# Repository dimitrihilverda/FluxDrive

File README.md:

# FluxDrive

An Amiga floppy drive emulator built around one ESP32-S3: no Gotek, no second microcontroller. It plugs into the
A500's internal floppy connector, holds a disk image in PSRAM and generates the MFM flux stream itself. Disk
images come from the [GTi](https://github.com/mesarim/Gotek-Touchscreen-interface) touchscreen over ESP-NOW, or
from a phone over WiFi. The design starts from Mez's OMEGAWARE FluxDrive hardware design document (see
[Credits](#credits)).

Status: v1 hardware (rev A) designed and reviewed: schematic, 4-layer layout (DRC clean) and JLCPCB production
files. It can be ordered once the checks under [Before ordering](#before-ordering) pass. Not built yet; the
firmware is a separate project.

| Where | What |
|---|---|
| `docs/superpowers/specs/` | design specs (start with the v1 hardware design) |
| `docs/input/` | the documents this design builds on: Mez's OMEGAWARE FluxDrive HW design v0.1, breadboard measurements |
| `docs/reviews/` | specialist reviews of the spec, schematic and layout, with what was done about each finding |
| `FluxDrive_Schematic.pdf` | the schematic (generated from `hardware/design.py` by `tools/sch_gen.py`) |
| `FluxDrive.kicad_pcb` | the board (built by `tools/pcb_build.sh`; KiCad 10) |
| `jlcpcb/production_files/` | gerbers and drill files (zip), BOM and CPL for JLCPCB (`tools/jlc_production.sh`) |
| `mech/` | 1:1 fit template (PDF) and a STEP model for a printed dummy (`tools/fit_template.sh`) |
| `docs/images/` | renders of the board, top and bottom |

Related: the breadboard prototype and its firmware live in
[dimitrihilverda/amiga-floppy-emulator](https://github.com/dimitrihilverda/amiga-floppy-emulator).

## Building one

The board is 60 × 54.5 mm, 4 layers. JLCPCB places every SMD part on the top side except the ESP32 module; the
module and the connectors are soldered by hand.

### Before ordering

- **Range test:** check the radio with a WROOM-1 dev board inside the closed A500 (spec §11.5). If the range is
  poor, rev A is not the board to order (the WROOM-1U with an external antenna is the fallback).
- **J1:** check the drawing of the box header C601943: its body must not be longer than 52 mm, or it overhangs
  the east edge (the footprint is 50.84 mm, DIN 41651).
- **J2:** check the outline of the TE 171825-4 (C210162) against its footprint (spec O15).
- **Fit:** print `mech/fit_template.pdf` at 100 % (both scale bars must measure 50 mm and 40 mm) and lay it on
  CN11 in the A500: pin 1 over pin 1, the "A500 FRONT" edge towards the front of the computer. Check that the
  drive's power cable from CN12 reaches J2 (about 6 cm) and that the room under the shield takes the tallest part
  (`mech/FluxDrive.step` has the heights; the USB-C, the buttons and the eFuse are missing from it, none taller
  than 3.3 mm). On Dimitri's A500 both are fine. The rectangle that reaches 14.5 mm past the north edge on the
  template is the module's antenna keep-out, not board.

### Order settings (JLCPCB)

Upload `jlcpcb/production_files/GERBER-FluxDrive.zip`:

| Setting | Value |
|---|---|
| Layers | 4 (the default stackup; no impedance control needed: USB is full speed only) |
| Size | 60 × 54.5 mm, single board (no panel) |
| Thickness | 1.6 mm |
| Surface finish | lead-free HASL or ENIG |
| Via covering | tented |
| Mark on PCB | order number at a specified position (the `JLCJLCJLCJLC` text on the bottom) |
| PCB assembly | yes: Economic (Standard if the form does not offer it for 4 layers), top side, 2 or 5 boards |

Then upload `BOM-FluxDrive.csv` and `CPL-FluxDrive.csv`. They hold the 86 SMD parts that JLC places. Left out
(`tools/jlc_export.py` lists them): the ESP32 module U1, which you place yourself (`tools/assembly.py`; its pads get
no solder paste, see below), the unfitted pads, the test pads, the fiducials and every through-hole part.

### Check in JLC's placement preview

Before paying, look at every part below in JLC's preview; fix a wrong rotation there.

- **U2, U3, U4** (74LVC14A, 74LVC07A, SOIC-14): pin 1 at the south-west corner of each. The CPL gives SOIC the same
  correction as the TSSOP that JLC placed on the Nano-Tek; the JLCPCB Tools default would be 270°.
- **U1** (ESP32-S3-WROOM-1) is not placed by JLC: the preview shows its pads empty, and they come without paste.
- **U5** (TPS259531, WSON-8 with exposed pad), **U6** (TLV62569, SOT-23-5), **U7** (USBLC6-2SC6, SOT-23-6):
  pin 1 dot.
- **D1, D2** (SS34): cathode band to the west. **D3** (LED): cathode to the west.
- **J3** (USB-C): the opening flush with the west edge (the shell reaches 0.18 mm past it).
- **SW1, SW2**: the four pads on the pads.

### Soldering by hand

| Ref | Part | LCSC | Notes |
|---|---|---|---|
| U1 | ESP32-S3-WROOM-1-N16R8 module (exactly this variant) | C2913202 | SMD: antenna to the north edge, pin 1 at the north-west. The pads come bare (no paste from JLC, so the module sits flat). Solder the large ground pad underneath (pin 41) too, for ground and heat: flux or paste on the pads, then hot air or a hot plate. An iron alone reaches only the edge pads. Solder it before the connectors, while the board still lies flat |
| J1 | 2×17 box header, 2.54 mm, vertical | C601943 | or, to plug the board straight onto CN11, a 2×17 female socket on the bottom side (see the note on the silkscreen); pin 1 is the square pad |
| J2 | TE 171825-4 floppy power header, vertical | C210162 | polarised; pin 1 = +5 V at the north end |
| J4 | 1×6 pin header, 2.54 mm | — | optional: UART recovery (TX, RX, EN, IO0, 3V3, GND from the ESP32's side) |
| J5 | 1×6 pin header, 2.54 mm | — | optional: spare GPIO13, 14, 47, 48, 3V3, GND |

- **J3's shell legs:** the four through-hole legs of the USB-C receptacle get no solder paste. Check them on
  delivery; if they are bare, solder them from the bottom side (they carry the plugging force, not the SMD pins).
- **After soldering J1:** `/CHNG_D` runs 0.25–0.30 mm past the row of J1's ground pins, on both sides. With the
  board unpowered, beep between U4 pin 10 (`/CHNG_D`) and J1 pin 1 (GND): a steady beep means a solder bridge or
  a scratched mask there, and the Amiga would see a disk change all the time.

The unfitted pads (0603 unless noted), only if bring-up asks for them: C1–C4 220 pF input filters on STEP, SEL0,
SEL1 and MTR0; R16 and R25 1 kΩ pull-ups for the two /MTR0 pins; C16 15 pF buck feed-forward; C21/C22 10 pF on
USB D+/D−; R49 1 Ω + C15 4.7 µF damper on V5SYS (then change C13 from 10 µF to 4.7 µF); D4 SMAJ13A TVS (SMA) on
the power input.

### Power: read this first

- The board takes its power from the A500's drive power connector CN12, through the drive's power cable on J2.
  **Never plug or unplug it with the A500 switched on.** A mini-Berg plug forced on the wrong way round puts
  +12 V on the 5 V pin: the eFuse survives that only when the plug goes on with the power off.
- +12 V (J2 pin 4) is not connected on the board.
- The 34-pin cable without the power cable is not supported: the bus pull-ups then hang on a dead rail.
- USB-C and the A500 may power the board at the same time; neither can feed the other.

### Flashing

Over USB-C: the ESP32-S3's USB-Serial/JTAG enters download mode by itself (`idf.py flash`, `esptool.py`). If the
firmware has taken GPIO19/20 or put the chip to sleep: hold BOOT, press and release RESET, release BOOT, and flash
again. If USB does not work at all, J4 takes a 3.3 V USB-serial adapter (its RX to J4 TX, its TX to J4 RX, GND;
IO0 to GND and a pulse on EN for download mode).

### Test pads

1.0 mm pads on the top side, for a probe. x from the west edge, y from the north (antenna) edge, in mm.

| Pad | Net | x | y | | Pad | Net | x | y |
|---|---|---|---|---|---|---|---|---|
| TP1 | /DKRD (connector) | 50.5 | 53.1 | | TP9 | /MTR0 (connector) | 32.7 | 53.1 |
| TP2 | DKRD_N (ESP32) | 42.6 | 31.8 | | TP10 | MTR0 (ESP32) | 30.8 | 33.7 |
| TP3 | /INDEX (connector) | 22.6 | 53.1 | | TP11 | +5V_A | 14.0 | 32.9 |
| TP4 | INDEX_N (ESP32) | 42.4 | 28.4 | | TP12 | V5SYS | 14.6 | 22.5 |
| TP5 | /SEL0 (connector) | 25.1 | 53.1 | | TP13 | VBUS | 12.2 | 22.6 |
| TP6 | SEL0 (ESP32) | 42.6 | 34.3 | | TP14 | +3V3 | 13.9 | 8.1 |
| TP7 | /STEP (connector) | 37.8 | 53.1 | | TP15 | ESP_EN | 13.9 | 11.8 |
| TP8 | STEP (ESP32) | 42.4 | 26.1 | | TP16 | GND | 55.6 | 53.1 |

The connector-side pads sit in the strip south of J1, each between two ground pins.

### Rebuilding the files

KiCad 10, Python 3 with pytest, Java 17 and Freerouting 1.9 (`~/.kicad-mcp/freerouting.jar`):

```bash
bash tools/export_netlist.sh && python -m pytest -q    # schematic and its tests
bash tools/pcb_build.sh                                # the board: placement, routing, DRC (15-60 min)
bash tools/jlc_production.sh                           # gerbers, BOM and CPL
```

## Credits

- **Mez** ([mesarim](https://github.com/mesarim)): the *OMEGAWARE FluxDrive Hardware Design Document, Rev 0.1*
  ([`docs/input/OMEGAWARE_FluxDrive_HW_Design_v0.1.md`](docs/input/OMEGAWARE_FluxDrive_HW_Design_v0.1.md)), the input
  this design is built on: one ESP32-S3 on the Shugart bus that generates the MFM flux itself and gets its disk
  images from the GTi over ESP-NOW, the bus interface, the bench gate and the bring-up order. The v1 spec says where
  it follows that document and where it departs from it.
- **Dimmy (Dimitri Hilverda)**: the v1 hardware, from the spec to the board and the production files.
- Disk images come from the [GTi](https://github.com/mesarim/Gotek-Touchscreen-interface) touchscreen.

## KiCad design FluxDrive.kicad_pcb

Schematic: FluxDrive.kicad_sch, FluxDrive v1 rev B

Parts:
C1, C2, C3, C4: 220pF; C_0603_1608Metric; not fitted
C5, C6, C7, C8, C9, C10, C16, C19, C21, C26, C30, C31, C32, C33, C36, C37, C38, C39, C40, C41, C42: 100nF; C_0402_1005Metric; LCSC C1525
C11, C13, C27, C34, C35: 1uF; C_0402_1005Metric; LCSC C52923
C12, C14: 22nF; C_0402_1005Metric; LCSC C1532
C15, C24, C25: 22uF; C_0805_2012Metric; LCSC C45783
C17, C18: 47uF; C_1206_3216Metric; LCSC C96123
C20: 10uF; C_0603_1608Metric; LCSC C19702
C22: 4.7uF; C_0603_1608Metric; not fitted
C23: 15pF; C_0603_1608Metric; not fitted
C28, C29: 10pF; C_0603_1608Metric; not fitted
C43, C44, C45: 100nF; C_0603_1608Metric; not fitted
D1, D2: SS34; D_SMA; LCSC C8678
D3: LED red; LED_0603_1608Metric; LCSC C2286
D4: SMAJ13A; D_SMA; not fitted
D5, D6: 1N4148W; D_SOD-123; LCSC C81598
FID1, FID2, FID3: Fiducial; Fiducial_1mm_Mask2mm
H1, H2: 3.2mm; MountingHole_3.2mm_M3
J1: Amiga floppy 34; IDC-Header_2x17_P2.54mm_Vertical; LCSC C601943
J2: Floppy power; 171825-4; LCSC C210162
J3: USB-C; USB-C-SMD_TYPE-C16PIN; LCSC C393939
J4: UART / recovery; PinHeader_1x06_P2.54mm_Vertical
J5: Spare / OLED; PinHeader_1x04_P2.54mm_Vertical
J6: Original drive; IDC-Header_2x17_P2.54mm_Vertical; LCSC C601943
J7: DF0 switch; PinHeader_1x03_P2.54mm_Vertical
J8: Drive power; 171825-4; LCSC C210162
J9: RST wire; TestPoint_THTPad_D1.5mm_Drill0.7mm
J10: MTRX wire; TestPoint_THTPad_D1.5mm_Drill0.7mm
JP1: bypass SEL; SolderJumper-3_P1.3mm_Bridged12_RoundedPad1.0x1.5mm
JP2: bypass MTR; SolderJumper-3_P1.3mm_Bridged12_RoundedPad1.0x1.5mm
JP3: mode 4 SEL; SolderJumper-3_P1.3mm_Bridged12_RoundedPad1.0x1.5mm
JP4: mode 4 MTR; SolderJumper-3_P1.3mm_Bridged12_RoundedPad1.0x1.5mm
JP5: DF0 at power-on; SolderJumper-3_P1.3mm_Bridged12_RoundedPad1.0x1.5mm
JP6: REAL clear; SolderJumper-2_P1.3mm_Open_RoundedPad1.0x1.5mm
JP7: REAL preset; SolderJumper-2_P1.3mm_Open_RoundedPad1.0x1.5mm
L1: 2.2uH; L_Sunlord_SWPA4020S; LCSC C83423
R1, R4, R7, R22, R25, R47, R76, R77: 4K7; R_0402_1005Metric; LCSC C25900
R2, R5, R8, R11, R15, R19, R23, R26, R28: 100; R_0402_1005Metric; LCSC C25076
R3, R6, R9, R12, R16, R20, R24, R27, R29, R32, R33, R51, R68, R69, R85: 100K; R_0402_1005Metric; LCSC C25741
R10, R13, R14, R17, R21, R53, R63, R70, R71, R74, R75, R83: 1K; R_0402_1005Metric; LCSC C11702
R18: 1K; R_0603_1608Metric; not fitted
R30: 4K7; R_0603_1608Metric; not fitted
R31: 100; R_0603_1608Metric; not fitted
R34, R36, R38, R40, R42, R44, R46, R55, R56, R59, R64, R65, R66, R67, R72, R73, R78, R79, R80, R82: 10K; R_0402_1005Metric; LCSC C25744
R35, R37, R39, R41, R43, R45, R81: 33; R_0402_1005Metric; LCSC C25105
R48: 2K2; R_0402_1005Metric; LCSC C25879
R49: 1K37; R_0402_1005Metric; LCSC C423239
R50: 1R; R_0603_1608Metric; not fitted
R52: 22K; R_0402_1005Metric; LCSC C25768
R54: 1K5; R_0402_1005Metric; LCSC C25867
R57, R58: 5K1; R_0402_1005Metric; LCSC C25905
R60, R61: 22; R_0402_1005Metric; LCSC C25092
R62: 470; R_0402_1005Metric; LCSC C25117
R84: 33; R_0603_1608Metric; not fitted
SW1: BOOT; SW_Push_1P1T_XKB_TS-1187A; LCSC C318884
SW2: RESET; SW_Push_1P1T_XKB_TS-1187A; LCSC C318884
TP1: _DKRD; TestPoint_Pad_D1.0mm
TP2: DKRD_N; TestPoint_Pad_D1.0mm
TP3: _INDEX; TestPoint_Pad_D1.0mm
TP4: INDEX_N; TestPoint_Pad_D1.0mm
TP5: _SEL0; TestPoint_Pad_D1.0mm
TP6: SEL0; TestPoint_Pad_D1.0mm
TP7: _STEP; TestPoint_Pad_D1.0mm
TP8: STEP; TestPoint_Pad_D1.0mm
TP9: _MTR0; TestPoint_Pad_D1.0mm
TP10: MTR0; TestPoint_Pad_D1.0mm
TP11: +5V_A; TestPoint_Pad_D1.0mm
TP12: V5SYS; TestPoint_Pad_D1.0mm
TP13: VBUS; TestPoint_Pad_D1.0mm
TP14: +3V3; TestPoint_Pad_D1.0mm
TP15: ESP_EN; TestPoint_Pad_D1.0mm
TP16: GND; TestPoint_Pad_D1.0mm
TP17: SEL_FD; TestPoint_Pad_D1.0mm
TP18: REAL_SEL; TestPoint_Pad_D1.0mm
TP19: REAL_MTR; TestPoint_Pad_D1.0mm
TP20: DF0_FD; TestPoint_Pad_D1.0mm
TP21: DF1_EN; TestPoint_Pad_D1.0mm
TP22: MODE_CLK; TestPoint_Pad_D1.0mm
U1: ESP32-S3-WROOM-1-N16R8; ESP32-S3-WROOM-1; LCSC C2913202
U2, U3: 74LVC14A; SOIC-14_3.9x8.7mm_P1.27mm; LCSC C133541
U4: 74LVC07A; SOIC-14_3.9x8.7mm_P1.27mm; LCSC C176925
U5, U9: TPS259531; Texas_DSG0008A_WSON-8-1EP_2x2mm_P0.5mm_EP0.9x1.6mm; LCSC C2155674
U6: TLV62569DBVR; SOT-23-5; LCSC C141836
U7: USBLC6-2SC6; SOT-23-6; LCSC C2687116
U8: 74LVC74A; TSSOP-14_4.4x5mm_P0.65mm; LCSC C6100
U10, U11: 74LVC32A; TSSOP-14_4.4x5mm_P0.65mm; LCSC C6087
U12, U13, U14, U15, U16: 74LVC1G157; SOT-363_SC-70-6; LCSC C135822
U17: SN74LVC2G07; SOT-23-6; LCSC C37708
U18: SN74LVC2G06; SOT-23-6; LCSC C402162
U19: SN74LVC1G06; SOT-23-5; LCSC C840103
U20: SN74LVC1G38; SOT-23-5; LCSC C2867613
U21: 74LVC1G157; SOT-363_SC-70-6; LCSC C135822; not fitted
U22: SN74LVC1G175; SOT-23-6; LCSC C128412; not fitted
U23: SN74LVC1G38; SOT-23-5; LCSC C2867613; not fitted

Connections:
/+3V3: C5.1, C6.1, C7.1, C8.1, C9.1, C10.1, C23.1, C24.1, C25.1, C26.1, C30.1, C31.1, C32.1, C33.1, C38.1, C39.1, C40.1, C41.1, C42.1, C43.1, C44.1, C45.1, D5.1 (K), D6.1 (K), J4.5, J5.2, JP7.2 (B), L1.2, R3.2, R6.2, R9.2, R12.2, R16.2, R20.2, R24.2, R27.2, R29.2, R32.2, R34.2, R36.2, R38.2, R40.2, R42.2, R44.2, R51.1, R55.1, R56.1, R64.2, R65.2, R66.2, R67.2, TP14.1, U1.2 (3V3), U2.14 (VCC), U3.14 (VCC), U4.9, U4.11, U4.14 (VCC), U7.5 (VBUS), U8.14 (VCC), U10.14 (VCC), U11.14 (VCC), U12.5 (VCC), U13.5 (VCC), U14.5 (VCC), U15.5 (VCC), U16.5 (VCC), U17.5 (VCC), U18.5 (VCC), U19.5 (VCC), U20.5 (VCC), U21.5 (VCC), U22.5 (VCC), U23.5 (VCC)
/+5V_A: C17.1, C18.1, C19.1, D1.2 (A), R1.2, R4.2, R7.2, R10.2, R14.2, R18.2, R22.2, R25.2, R30.2, R53.1, R76.2, R77.2, R78.2, R79.2, R80.2, TP11.1, U5.5 (OUT)
/+5V_DRIVE: C15.1, C16.1, J8.1 (5V), U9.5 (OUT)
/+5V_IN: C11.1, C13.1, D4.1 (A1), J2.1 (5V), R46.1, U5.3 (IN), U5.4 (IN), U9.3 (IN), U9.4 (IN)
/+12V: J2.4 (12V), J8.4 (12V)
/AMIGA_PWR: R53.2, R54.1, U1.39 (IO1)
/BOOT: J4.4, R56.2, SW1.1, U1.27 (IO0)
/BUCK_FB: C23.2, R51.2, R52.1, U6.5 (FB)
/BUCK_SW: L1.1, U6.3 (SW)
/BUSY: U11.8, U16.6 (S)
/CHNG_D: R43.1, U17.6
/CHNG_G: U11.3, U17.1
/CHNG_N: R42.1, U1.35 (IO42), U11.1
/CHNG_REQ: R73.1, U1.22 (IO14), U20.1
/CLR_A: JP5.1 (A), JP6.1 (A), R64.1, R75.2, U8.1 (~R)
/CLR_B: C34.1, D5.2 (A), R66.1, U8.13 (~R)
/DF0_FD: R68.1, R70.1, TP20.1, U8.5 (Q), U13.6 (S), U14.6 (S), U15.6 (S), U21.6 (S)
/DF0_REQ: R68.2, U1.25 (IO48), U8.2 (D)
/DF0_STATE: R70.2, U1.20 (IO12)
/DF1_EN: R69.1, R71.1, TP21.1, U8.9 (Q), U12.6 (S), U22.6 (~CLR)
/DF1_REQ: R69.2, U1.21 (IO13), U8.12 (D)
/DF1_STATE: R71.2, U1.12 (IO8)
/DIR: U1.7 (IO7), U2.2
/DIR_B: R5.2, R6.1, U2.1
/DKRD_D: R35.1, U4.4
/DKRD_G: U4.3, U10.3
/DKRD_N: R34.1, TP2.1, U1.31 (IO38), U10.1
/DKWD: U1.5 (IO5), U2.4
/DKWD_B: R23.2, R24.1, U2.3
/DKWE: U1.9 (IO16), U2.10
/DKWE_B: R26.2, R27.1, U2.11
/DRV_DVDT: C14.1, U9.1 (dVdt)
/DRV_ILM: R49.1, U9.7 (ILM)
/EFUSE_DVDT: C12.1, U5.1 (dVdt)
/EFUSE_EN: R46.2, R47.1, U5.2 (EN/UVLO), U9.2 (EN/UVLO)
/EFUSE_ILM: R48.1, U5.7 (ILM)
/ESP_EN: C27.1, J4.3, R55.2, SW2.1, TP15.1, U1.3 (EN)
/ESP_RXD0: J4.2, U1.36 (RXD0)
/ESP_TXD0: R62.1, U1.37 (TXD0)
/GND: C1.2, C2.2, C3.2, C4.2, C5.2, C6.2, C7.2, C8.2, C9.2, C10.2, C11.2, C12.2, C13.2, C14.2, C15.2, C16.2, C17.2, C18.2, C19.2, C20.2, C21.2, C22.2, C24.2, C25.2, C26.2, C27.2, C28.2, C29.2, C30.2, C31.2, C32.2, C33.2, C34.2, C35.2, C36.2, C37.2, C38.2, C39.2, C40.2, C41.2, C42.2, C43.2, C44.2, C45.2, D3.1 (K), D4.2 (A2), J1.1, J1.5, J1.7, J1.9, J1.11, J1.13, J1.15, J1.17, J1.19, J1.21, J1.23, J1.25, J1.27, J1.29, J1.31, J1.33, J2.2 (GND), J2.3 (GND), J3.1 (SHELL), J3.2 (SHELL), J3.3 (SHELL), J3.4 (SHELL), J3.A1B12 (GND), J3.B1A12 (GND), J4.6, J5.1, J6.1, J6.5, J6.7, J6.9, J6.11, J6.13, J6.15, J6.17, J6.19, J6.21, J6.23, J6.25, J6.27, J6.29, J6.31, J6.33, J7.2, J8.2 (GND), J8.3 (GND), JP3.1 (A), JP4.1 (A), JP6.2 (B), R33.2, R47.2, R48.2, R49.2, R52.2, R54.2, R57.2, R58.2, R59.2, R72.2, R73.2, R82.2, R85.2, SW1.2, SW2.2, TP16.1, U1.1 (GND), U1.40 (GND), U1.41 (GND), U2.7 (GND), U3.7 (GND), U4.7 (GND), U5.8 (GND), U5.9 (PAD), U6.2 (GND), U7.2 (GND), U8.7 (GND), U9.8 (GND), U9.9 (PAD), U10.7 (GND), U11.7 (GND), U11.12, U11.13, U12.2 (GND), U12.3 (I0), U13.2 (GND), U14.2 (GND), U15.2 (GND), U16.1 (I1), U16.2 (GND), U17.2 (GND), U18.2 (GND), U19.3 (GND), U20.3 (GND), U21.2 (GND), U21.3 (I0), U22.2 (GND), U23.3 (GND)
/GPIO3: J5.4, U1.15 (IO3)
/GPIO18: J5.3, U1.11 (IO18)
/ID_D: R84.1, U23.4
/INDEX_D: R45.1, U17.4
/INDEX_G: U11.6, U17.3
/INDEX_N: R44.1, TP4.1, U1.32 (IO39), U11.4
/J6_MTR: J6.4, J6.16, JP2.2 (C)
/J6_MTR_D: JP2.1 (A), R77.1, U18.4
/J6_PIN6: J6.6, R78.1
/J6_PIN12: J6.12, R79.1
/J6_PIN14: J6.14, R80.1
/J6_SEL: J6.10, JP1.2 (C)
/J6_SEL_D: JP1.1 (A), R76.1, U18.6
/J7_FD: C36.1, J7.1, R74.1
/J7_REAL: C37.1, J7.3, R75.1
/KBRESET: J9.1, R28.1, U19.4
/LED: R63.1, U1.38 (IO2)
/LED_A: D3.2 (A), R63.2
/M4_MOTOR: U3.6, U22.3 (D)
/M4_MTR: JP4.2 (C), U15.1 (I1)
/M4_MTR_N: U3.12, U23.2
/M4_MTR_Q: JP4.3 (B), R33.1, U3.13, U22.4 (Q)
/M4_SEL: JP3.2 (C), U14.1 (I1)
/M4_SEL_Q: JP3.3 (B), R85.1, U21.4 (Y), U23.1
/MODE_CLK: TP22.1, U8.3 (C), U8.11 (C), U16.4 (Y)
/MODE_CLK_REQ: R72.1, U1.24 (IO47), U16.3 (I0)
/MTR0: R21.1, TP10.1, U3.8, U15.3 (I0)
/MTR0_B: C4.1, R19.2, R20.1, U3.9
/MTR0_IO: R21.2, U1.19 (IO11)
/MTRX: J10.1, R30.1, R31.1
/MTRX_B: R31.2, R32.1, U3.5
/POR_A: C35.1, D6.2 (A), JP5.2 (C)
/PRE_A: JP5.3 (B), JP7.1 (A), R65.1, R74.2, U8.4 (~S)
/PRE_B: R67.1, U8.10 (~S)
/RDY_D: R41.1, U4.6
/RDY_G: U4.5, U10.11
/RDY_N: R40.1, U1.23 (IO21), U10.12
/REAL_MTR: TP19.1, U15.4 (Y), U18.3
/REAL_SEL: TP18.1, U14.4 (Y), U18.1
/RST_ACT: R83.1, U3.2
/RST_ACT_IO: R83.2, U1.4 (IO4)
/RST_B: R28.2, R29.1, U3.1
/RST_REQ: R82.1, U1.18 (IO10), U19.2
/SEL0: R13.1, TP6.1, U3.4, U11.9, U13.1 (I1), U14.3 (I0), U20.2
/SEL0_B: C2.1, R11.2, R12.1, U3.3
/SEL0_IO: R13.2, U1.10 (IO17)
/SEL1: R17.1, U3.10, U11.10, U12.1 (I1), U22.1 (C)
/SEL1_B: C3.1, R15.2, R16.1, U3.11
/SEL1_EN: U12.4 (Y), U13.3 (I0), U21.1 (I1)
/SEL1_IO: R17.2, U1.17 (IO9)
/SEL_FD: TP17.1, U2.9, U13.4 (Y)
/SEL_FD_N: U2.8, U10.2, U10.5, U10.10, U10.13, U11.2, U11.5
/SIDE: U1.8 (IO15), U2.6
/SIDE_B: R8.2, R9.1, U2.5
/STEP: TP8.1, U1.6 (IO6), U2.12
/STEP_B: C1.1, R2.2, R3.1, U2.13
/TRK0_D: R37.1, U4.12
/TRK0_G: U4.13, U10.6
/TRK0_N: R36.1, U1.33 (IO40), U10.4
/UART_TX: J4.1, R62.2
/USB_CC1: J3.A5 (CC1), R57.1
/USB_CC2: J3.B5 (CC2), R58.1
/USB_DN: C29.1, R61.2, U1.13 (USB_D-)
/USB_DN_C: J3.A7 (DN1), J3.B7 (DN2), R61.1, U7.1 (I/O1), U7.6 (I/O1)
/USB_DP: C28.1, R60.2, U1.14 (USB_D+)
/USB_DP_C: J3.A6 (DP1), J3.B6 (DP2), R60.1, U7.3 (I/O2), U7.4 (I/O2)
/V5SYS: C20.1, C21.1, D1.1 (K), D2.1 (K), R50.1, TP12.1, U6.1 (EN), U6.4 (VIN)
/V5SYS_DAMP: C22.1, R50.2
/VBUS: D2.2 (A), J3.A4B9 (VBUS), J3.B4A9 (VBUS), R59.1, TP13.1
/VCHNG_D: R81.1, U20.4
/WPROT_D: R39.1, U4.2
/WPROT_G: U4.1, U10.8
/WPROT_N: R38.1, U1.34 (IO41), U10.9
/_CHNG: J1.2, J6.2, R43.2, R81.2
/_DIR: J1.18, J6.18, R4.1, R5.1
/_DKRD: J1.30, J6.30, R35.2, TP1.1
/_DKWD: J1.22, J6.22, R22.1, R23.1
/_DKWE: J1.24, J6.24, R25.1, R26.1
/_INDEX: J1.8, J6.8, R45.2, TP3.1
/_MTR0: J1.16, JP2.3 (B), R18.1, R19.1, TP9.1
/_RDY: J1.34, J6.34, R41.2, R84.2
/_SEL0: J1.10, JP1.3 (B), R10.1, R11.1, TP5.1
/_SEL1: J1.12, R14.1, R15.1
/_SIDE: J1.32, J6.32, R7.1, R8.1
/_STEP: J1.20, J6.20, R1.1, R2.1, TP7.1
/_TRK0: J1.26, J6.26, R37.2
/_WPROT: J1.28, J6.28, R39.2

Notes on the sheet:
A. Floppy connector and bus inputs
B. Bus outputs
C. Power
D. ESP32-S3 module
E. USB-C
F. Headers, buttons, LED, test pads, mechanics
G. Drive pass-through and DF0/DF1 swap

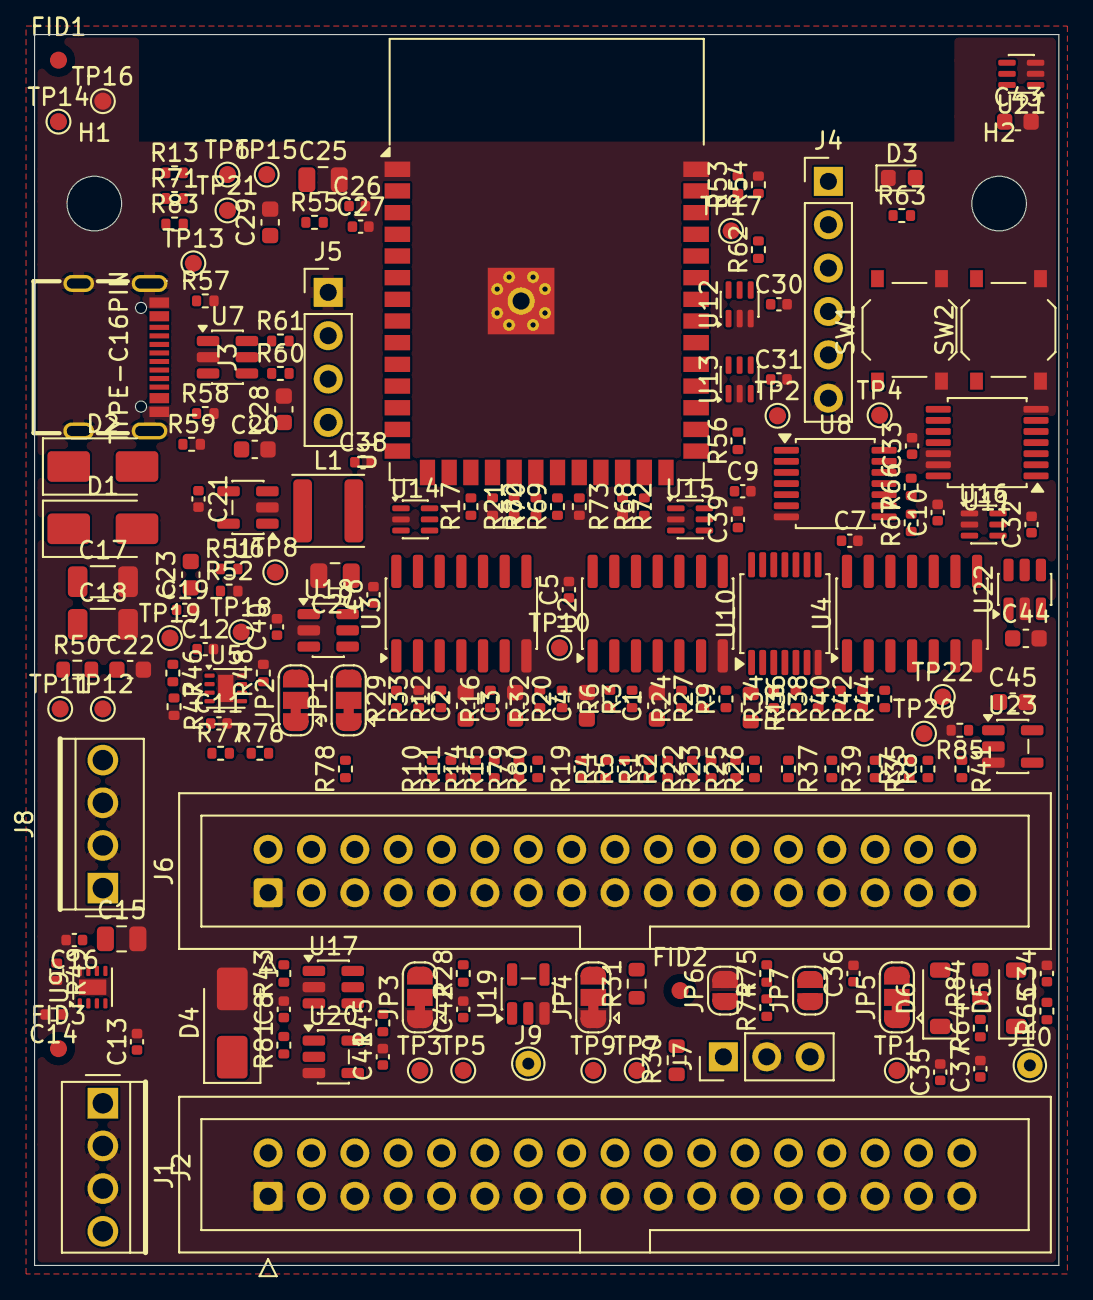
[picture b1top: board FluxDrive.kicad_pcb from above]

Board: 4 copper layers, 60.0 x 72.1 mm, 206 parts (0 on the bottom side), 127 nets, no tracks yet.

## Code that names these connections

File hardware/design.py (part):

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# --- A: connector and inputs -----------------------------------------------------------------------------
EVEN = {2: "_CHNG", 4: None, 6: None, 8: "_INDEX", 10: "_SEL0", 12: "_SEL1", 14: None,
        16: "_MTR0", 18: "_DIR", 20: "_STEP", 22: "_DKWD", 24: "_DKWE", 26: "_TRK0", 28: "_WPROT",
        30: "_DKRD", 32: "_SIDE", 34: "_RDY"}          # rev B spec §7: pins 4, 6, 14 are not used on the A500
j1 = {str(p): ("GND" if p != 3 else None) for p in range(1, 34, 2)}
j1.update({str(p): n for p, n in EVEN.items()})
part("J1", "Connector_Generic:Conn_02x17_Odd_Even", "Amiga floppy 34", "Connector_IDC:IDC-Header_2x17_P2.54mm_Vertical",
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GPIO_NET = {}
buf = {"U2": {"14": "+3V3", "7": "GND", "9": "SEL_FD", "8": "SEL_FD_N"},   # U2's spare makes SEL_FD_N (§4.2)
       "U3": {"14": "+3V3", "7": "GND",
              "1": "RST_B", "2": "RST_ACT",              # rev A's J1 pin 4 gate: the reset wire (§4.8)
              "5": "MTRX_B", "6": "M4_MOTOR",            # rev A's pin 14 gate: mode 4's motor line (§4.7)
              "13": "M4_MTR_Q", "12": "M4_MTR_N"}}       # rev A's pin 6 gate: NOT M4_MTR for the DF1 ID (§4.7)
for sig, conn, pull, gpio, u, pin_in, pin_out, cpad, iso in INPUTS:
    if pull:
        R(pull[0], conn, pull[1], A)
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for sig, conn, gpio, bufr, pin_in, pin_out, orc, (a, b, y) in OUTPUTS:
    R("10K", f"{sig}_N", "+3V3", B)                 # release pull-up, on the OR input (rev B §4.3)
    R("33", f"{sig}_D", conn, B)
    pins_of[orc].update({str(a): f"{sig}_N", str(b): "SEL_FD_N", str(y): f"{sig}_G"})
    pins_of[bufr].update({str(pin_in): f"{sig}_G", str(pin_out): f"{sig}_D"})
    GPIO_NET[gpio] = f"{sig}_N"
part("U4", "74xx:74LCX07", "74LVC07A", SOIC14, pins_of["U4"], B,      # Diodes 74LVC07AS14-13, SO-14
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C("22uF", "+3V3", "GND", P)
R("1K", "+5V_A", "AMIGA_PWR", P)            # 3.0 V at 5 V, 3.5 V at the clamp; stiff enough that the bus
R("1K5", "AMIGA_PWR", "GND", P)             # pull-ups cannot lift it on USB alone (review SESP-1)
PWR_FLAGS = ["GND", "+3V3", "+5V_IN", "V5SYS", "VBUS"]          # +5V_A is driven by the eFuse OUT pin

# --- D: ESP32-S3 module --------------------------------------------------------------------------------------
esp = {"1": "GND", "40": "GND", "41": "GND", "3V3": "+3V3", "EN": "ESP_EN", "IO0": "BOOT", "IO1": "AMIGA_PWR",
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for gpio, net in GPIO_NET.items():
    esp[f"IO{gpio}"] = net
esp.update({"IO47": "MODE_CLK_REQ", "IO48": "DF0_REQ", "IO13": "DF1_REQ", "IO14": "CHNG_REQ",
            "IO10": "RST_REQ", "IO12": "DF0_STATE", "IO8": "DF1_STATE", "IO4": "RST_ACT_IO", "IO18": "GPIO18",
            "IO3": "GPIO3"})
part("U1", "RF_Module:ESP32-S3-WROOM-1", "ESP32-S3-WROOM-1-N16R8", "FluxDrive:ESP32-S3-WROOM-1", esp, E,
     lcsc="C2913202")
C("22uF", "+3V3", "GND", E)
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     {"1": "UART_TX", "2": "ESP_RXD0", "3": "ESP_EN", "4": "BOOT", "5": "+3V3", "6": "GND"}, F, in_bom=False)
HDR4 = "Connector_PinHeader_2.54mm:PinHeader_1x04_P2.54mm_Vertical"
part("J5", "Connector_Generic:Conn_01x04", "Spare / OLED", HDR4,              # rev B §7: GND 3V3 SCL SDA order
     {"1": "GND", "2": "+3V3", "3": "GPIO18", "4": "GPIO3"}, F, in_bom=False)
R("1K", "LED", "LED_A", F)
part("D3", "Device:LED", "LED red", "LED_SMD:LED_0603_1608Metric", {"1": "GND", "2": "LED_A"}, F, lcsc="C2286")
for net in ("_DKRD", "DKRD_N", "_INDEX", "INDEX_N", "_SEL0", "SEL0", "_STEP", "STEP", "_MTR0", "MTR0",
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part("JP4", JP3B[0], "mode 4 MTR", JP3B[2], {"1": "GND", "2": "M4_MTR", "3": "M4_MTR_Q"}, G, in_bom=False)
j6 = {str(p): ("GND" if p != 3 else None) for p in range(1, 34, 2)}
j6.update({str(p): EVEN[p] for p in (2, 8, 18, 20, 22, 24, 26, 28, 30, 32, 34)})
j6.update({"4": "J6_MTR", "16": "J6_MTR", "10": "J6_SEL", "6": "J6_PIN6", "12": "J6_PIN12", "14": "J6_PIN14"})
part("J6", "Connector_Generic:Conn_02x17_Odd_Even", "Original drive", "Connector_IDC:IDC-Header_2x17_P2.54mm_Vertical",
     j6, G, lcsc="C601943")
for net in ("J6_PIN6", "J6_PIN12", "J6_PIN14"):
    R("10K", net, "+5V_A", G)
part("U20", "74xGxx:74LVC1G38", "SN74LVC1G38", "Package_TO_SOT_SMD:SOT-23-5",
     {"1": "CHNG_REQ", "2": "SEL0", "4": "VCHNG_D", "3": "GND", "5": "+3V3"}, G, lcsc="C2867613")
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R("1K", "RST_ACT", "RST_ACT_IO", G)
TP_THT = "TestPoint:TestPoint_THTPad_D1.5mm_Drill0.7mm"
part("J9", "Connector:TestPoint", "RST wire", TP_THT, {"1": "KBRESET"}, G, in_bom=False)   # to _KBRESET (§4.8)
part("J10", "Connector:TestPoint", "MTRX wire", TP_THT, {"1": "MTRX"}, G, in_bom=False)   # to CIA-B pin 17 (§4.7)
mux("U21", "DF0_FD", "GND", "SEL1_EN", "M4_SEL_Q", dnp=True)   # M4_SEL = DF0_FD AND SEL1_EN
part("U22", "74xGxx:74LVC1G175", "SN74LVC1G175", "Package_TO_SOT_SMD:SOT-23-6",   # SN74LVC1G175DBVR
     {"1": "SEL1", "3": "M4_MOTOR", "6": "DF1_EN", "4": "M4_MTR_Q", "2": "GND", "5": "+3V3"}, G, lcsc="C128412",
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
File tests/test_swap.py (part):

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def test_control_gpios(nl):
    """Rev B spec §7: the GPIO map; outputs active-high with 10k pull-downs, read-backs through 1k."""
    want = {47: "MODE_CLK_REQ", 48: "DF0_REQ", 13: "DF1_REQ", 14: "CHNG_REQ", 12: "DF0_STATE", 8: "DF1_STATE",
            18: "GPIO18", 3: "GPIO3"}
    for gpio, net in want.items():
        assert esp_net(nl, gpio) == net, gpio
    for net in ("MODE_CLK_REQ", "CHNG_REQ"):
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    for p in J6_1TO1:
        assert nl.net_of("J6", p) == nl.net_of("J1", p), p
    assert nl.net_of("J6", 10) == "J6_SEL" and nl.net_of("J6", 4) == nl.net_of("J6", 16) == "J6_MTR"
    for p, net in ((6, "J6_PIN6"), (12, "J6_PIN12"), (14, "J6_PIN14")):
        assert nl.net_of("J6", p) == net and pulls(nl, net) == [("10K", "+5V_A")], p
    for p in range(1, 35, 2):
        assert (nl.net_of("J6", p) or "").startswith("unconnected-") if p == 3 else nl.net_of("J6", p) == "GND"
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    from tests.logic import evaluate
    v = evaluate(nl, {"_CHNG": (1, 1), "_INDEX": (1, 1), "_TRK0": (1, 1), "_WPROT": (1, 1), "_DKRD": (1, 1),
                      "_RDY": (1, 1), "KBRESET": (1, 1)})
    for net in ("J6_SEL", "J6_MTR", "J6_PIN6", "J6_PIN12", "J6_PIN14"):
        assert v[net] == 1, net


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    assert [nl.net_of("U22", p) for p in (1, 3, 6, 4)] == ["SEL1", "M4_MOTOR", "DF1_EN", "M4_MTR_Q"]
    assert {nl.net_of("U23", 1), nl.net_of("U23", 2)} == {"M4_SEL_Q", "M4_MTR_N"} and nl.net_of("U23", 4) == "ID_D"
    from tests.fd import dnp_between
    assert len(dnp_between(nl, "ID_D", "_RDY", "R")) == 1
    assert nl.net_of("J10", 1) == "MTRX"


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def test_reset_wire(nl):
    assert nl.net_of("J9", 1) == "KBRESET"
    assert not pulls(nl, "KBRESET")                              # no pull-up on the pad: RP501 on the motherboard
    assert [value(nl, r) for r in parts_between(nl, "KBRESET", "RST_B")] == ["100"]      # into U3 pin 1 (§4.8)
    assert value(nl, "U19") == "SN74LVC1G06"
    assert (nl.net_of("U19", 2), nl.net_of("U19", 4)) == ("RST_REQ", "KBRESET")
    assert pulls(nl, "RST_REQ") == [("10K", "GND")]
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    for bridged, stored in (({"J7": [("1", "2")]}, 0), ({}, 1)):          # J7 on FD; or the GTi chose FD
        bridged = {**bridged, "JP1": [("2", "3")], "JP2": [("2", "3")]}
        v = evaluate(nl, amiga(1, 0, 0), state={("U8", "A"): stored, ("U8", "B"): 0}, bridged=bridged)
        assert v["SEL_FD"] == 1 and v["J6_SEL"] == 0


@pytest.mark.parametrize("pattern", range(64))
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    power-on, so a drive strapped DS1-DS3 never answers next to FluxDrive."""
    for df0, df1, sel0, sel1, mtr0 in itertools.product((0, 1), repeat=5):
        v = evaluate(nl, amiga(sel0, sel1, mtr0), state={("U8", "A"): df0, ("U8", "B"): df1})
        for net in ("J6_PIN6", "J6_PIN12", "J6_PIN14"):
            assert v[net] == 1, (net, df0, df1, sel0, sel1, mtr0)


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    b.set(_SEL0=(0, OD))                                   # real drive DF0, being read
    b.set(DF0_REQ=(1, STRONG))                             # D first, then the clock request (spec §8)
    b.set(MODE_CLK_REQ=(1, STRONG))
    assert b.v["DF0_FD"] == 0 and b.v["REAL_SEL"] == 1 and b.v["MODE_CLK"] == 0
    b.set(_SEL0=None)                                      # access over: the clock arrives
    assert b.v["DF0_FD"] == 1 and b.v["REAL_SEL"] == 0
    b.set(MODE_CLK_REQ=(0, STRONG))
    assert b.v["DF0_FD"] == 1


def test_request_dropped_inside_an_access_is_lost(nl):
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    b.set(MODE_CLK_REQ=(1, STRONG))
    b.set(MODE_CLK_REQ=(0, STRONG))
    b.set(_SEL1=None)
    assert b.v["DF0_FD"] == 0 and b.v["DF1_EN"] == 1


def test_switch_moved_during_an_access(nl):
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    the centre; it never touches DF1_EN."""
    b = Board(nl, stored=(0, 1))                           # mode 3
    b.set(_SEL0=(0, OD))                                   # the real drive, DF0, is being read
    assert b.v["REAL_SEL"] == 1 and b.v["SEL_FD"] == 0
    b.throw("FD")
    assert (b.v["DF0_FD"], b.v["DF1_EN"], b.v["REAL_SEL"], b.v["SEL_FD"]) == (1, 1, 0, 1)
    b.throw("GTi")
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

def test_esp32_reset_changes_nothing(nl):
    """Review focus 4: control GPIOs undriven, with their internal pull-ups on: no clock, no /CHNG, no reset, and
    /RDY and the J6 lines idle, checked during an access (where /CHNG and J6.10 could show it) and after it."""
    for stored in ((0, 0), (1, 0), (0, 1)):
        b = Board(nl, stored=stored)
        assert_idle(b.set(_SEL0=(0, OD)), stored, 1, "access, GPIOs undriven")
        assert_idle(b.set(**{n: (1, WEAK) for n in ("MODE_CLK_REQ", "DF0_REQ", "DF1_REQ", "CHNG_REQ", "RST_REQ")}),
                    stored, 1, "access, internal pull-ups on")
        b.set(_SEL0=None)
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    """Rev B §4.1, §10.1: GPIO1-17 driven low for 60 us at an ESP32 reset, in every mode, with and without an
    access: no clock, no /CHNG, no reset pulse, the mode kept, the real drive's select follows the bus."""
    glitch = ("RST_ACT_IO", "DF1_STATE", "SEL1_IO", "RST_REQ", "MTR0_IO", "DF0_STATE", "DF1_REQ", "CHNG_REQ",
              "SEL0_IO")                                  # GPIO 4, 8, 9, 10, 11, 12, 13, 14, 17
    for stored in ((0, 0), (1, 0), (0, 1)):
        for sel0 in (0, 1):
            b = Board(nl, stored=stored)
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    for _ in range(3):
        b.set(MTRX=(0, OD))
        b.set(_SEL1=(0, OD))
        assert b.v["J6_MTR"] == 1 and b.v["J6_SEL"] == 1 and b.v["_RDY"] == 1
        b.set(_SEL1=None)
        b.set(MTRX=None)

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    assert (b.v["J6_MTR"], b.v["J6_SEL"]) == (0, 1)                        # deselected, the motor runs on
    b.set(_SEL1=(0, OD))
    b.set(_SEL1=None)
    assert b.v["J6_MTR"] == 0                                              # a second access keeps it on
    b.set(MTRX=None)
    assert b.v["J6_MTR"] == 0                                              # motor bit off, no edge yet: still on
    b.set(_SEL1=(0, OD))
    assert (b.v["J6_MTR"], b.v["J6_SEL"], b.v["_RDY"]) == (1, 0, 0)        # latched off: the DD ID on /RDY
    b.set(_SEL1=None)
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            assert v["SEL_FD"] == e["SEL_FD"] and v["J6_SEL"] == 1 - e["REAL_SEL"], (node, ev)
            assert not (v["MODE_CLK"] and (n["sel0"] or n["sel1"])), (node, ev)
            moved = (v["DF0_FD"], v["DF1_EN"]) != (before["DF0_FD"], before["DF1_EN"])
            clocked = before["MODE_CLK"] == 0 and v["MODE_CLK"] == 1
            assert not moved or ev == "sw" or clocked, (node, ev)
            nxt = (b.state[("U8", "A")], b.state[("U8", "B")], n["sel0"], n["sel1"], n["req0"], n["req1"],
                   n["clk"], nsw)
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
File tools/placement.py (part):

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
def j6_pull_ups():
    """J6.6, 12 and 14's 10 kOhm in row A's free columns (review B6): pins 6 and 14 carry no J1 net in rev B."""
    return {R("J6_PIN6", "+5V_A"): (round(pin_x(6) - 0.55, 3), ROW_A, 90),
            R("J6_PIN12", "+5V_A"): (round(pin_x(14) - 0.55, 3), ROW_A, 90),
            R("J6_PIN14", "+5V_A"): (round(pin_x(14) + 0.55, 3), ROW_A, 90)}


def fixed():
    """Parts that go exactly where the table says."""
    out = {
        "J1": (J1_PIN1[0], J1_PIN1[1], 90),
        "J6": (J6_PIN1[0], J6_PIN1[1], 90),          # same orientation, pin 1 on the same side (spec 9)
        "U1": (130.0, round(UY, 3), 0),
        "J2": (104.0, 136.1, 270),                   # pin 1 (+5 V) north; 0.4 mm north of rev A: its courtyard ends
                                                     # inside the new south edge
        "J8": (104.0, 123.5, 90),                    # J6pwr: pin 1 south towards U9, pin 4 north
        "J3": (104.945, n(112.5), 270),              # USB-C, opening to the west edge
        "U3": (125.0, BUF_Y, 90),                    # 74LVC14A: J1 pins 10-16 and the freed gates
        "U2": (136.5, BUF_Y, 90),                    # 74LVC14A: J1 pins 18-32, SEL_FD_N
        "U4": (151.4, BUF_Y, 90),                    # 74LVC07A, 1.4 mm east of rev A: U10 sits between U2 and U4
        "H1": (103.5, n(103.5), 0),
        "H2": (156.5, n(103.5), 0),
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    a((C("+3V3", "GND", after="U3"), 119.8, BUF_Y - 1.4, 90))
    a((C("+3V3", "GND", after="U2"), 131.3, BUF_Y - 1.4, 90))
    a((C("+3V3", "GND", after="U4"), 147.75, BUF_Y - 4.27, 0))
    # --- row M: the GPIO-side 0402s straight under the module's bottom pins 17-25 -------------------------------
    for pin_n, x, ref, rot in (
            (17, 125.555, R("SEL1", "SEL1_IO"), 90), (18, 126.825, R("RST_REQ", "GND"), 270),
            (19, 128.095, R("MTR0", "MTR0_IO"), 90), (20, 129.365, R("DF0_FD", "DF0_STATE"), 90),
            (21, 130.635, R("DF1_EN", "DF1_REQ"), 90), (22, 131.905, R("CHNG_REQ", "GND"), 270),
            (24, 134.445, R("MODE_CLK_REQ", "GND"), 270), (25, 135.715, R("DF0_FD", "DF0_REQ"), 90)):
        a((ref, x, round(ROW_M, 3), rot))
    # the left-side GPIO 1 kOhms (GPIO17 SEL0, GPIO8 DF1_STATE, GPIO4 RST_ACT) beside their module pins
    a((R("SEL0", "SEL0_IO"), 108.2, 81.6, 0))                      # clear of the antenna border's vias
    a((R("DF1_EN", "DF1_STATE"), 108.2, 83.1, 0))
    a((R("RST_ACT", "RST_ACT_IO"), 108.2, 84.6, 0))
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    a(("U14", 122.3, gy, 0))                                       # REAL_SEL, west of row M
    a(("U15", 138.4, gy, 0))                                       # REAL_MTR, east of row M
    a(("U12", 141.3, 89.3, 90))                                    # SEL1_EN, east of the module
    a(("U13", 141.3, 93.7, 90))                                    # SEL_FD, down to U2 pin 9
    a(("U10", 143.95, BUF_Y, 90))                                  # ORs for U4, between U2 and U4
    a(("U8", 146.9, 99.8, 0))                                      # the mode latch
    a((R("+3V3", "CLR_B"), 151.35, 100.0, 90))
    a((R("+3V3", "PRE_B"), 151.35, 102.1, 90))
    a(("U11", 155.8, 97.4, 180))                                   # CHNG/INDEX ORs and BUSY; pin 14 south-west
    a(("U16", 155.6, 102.2, 0))                                    # the clock gate, next to BUSY
    a((C("+3V3", "GND", after="U8"), 151.4, 97.6, 90))
    a((C("+3V3", "GND", after="U11"), 152.9, 101.5, 90))
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    a((C("+3V3", "GND", after="U22"), 158.0, 108.8, 0))
    a((C("+3V3", "GND", after="U23"), 157.3, 112.6, 0))
    a(("U23", 157.3, 115.2, 0))
    a((R("M4_SEL_Q", "GND"), 154.2, 114.25, 180))                 # the 100 kOhm west of U23's input pin 1 (pad 1 east),
                                                                  # as R33 on U3's
    # --- row B: rev A's 100 kOhm at the buffer inputs, spread so each 220 pF sits beside its own 100 kOhm -------
    for x, ref in ((121.2, R("+3V3", "RST_B")), (122.5, R("GND", "M4_MTR_Q")), (123.8, R("+3V3", "SEL0_B")),
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    # --- the J1-J6 band: parts that meet the pass-through nets, the builder's jumpers and pads ---------------
    # Pads stay out of the pass-through tracks' strips (corridors()); parts in different gaps meet on B.Cu.
    lo, hi = BAND
    # pins 4-6 column: U17 with its 33 ohm to J1 pins 2 and 8 (rev B spec 4.3), U20 with its 33 ohm on /CHNG
    a(("U17", 117.5, lo + 1.8, 0))
    a(("U20", 117.5, hi - 1.9, 0))
    a((R("CHNG_D", "_CHNG"), 114.6, lo + 1.0, 90))
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    a((TP("_DKRD"), gap_x(30), hi - 1.1, 0))
    a(("D6", gap_x(32), lo + 2.45, 90))
    a((C("GND", "POR_A"), gap_x(32), hi - 1.0, 90))
    # east end: the DD ID's 33 ohm on /RDY (J1 pin 34), flip-flop B's power-on RC, the other RCs, GND pad
    a((R("ID_D", "_RDY"), 155.4, lo + 1.6, 90))
    a((R("+3V3", "CLR_A"), 155.4, lo + 4.2, 90))
    a((C("GND", "J7_REAL"), 155.4, hi - 1.2, 90))
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    a((TP("ESP_EN"), 113.6, 81.7, 0))
    a((TP("GND"), 104.0, 77.4, 0))                                # its via is one of the border's west side
    a(("FID1", 101.4, 75.0, 0))
    # the spare header next to module pins 11 (IO18) and 15 (IO3), west side (rev B spec 7)
    a(("J5", 117.2, 88.6, 0))                                    # pin 3 (IO18) beside module pin 11
    return t

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
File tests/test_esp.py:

from tests.fd import between, esp_net, is_nc, parts_between, pulls


def test_module(nl):
    assert nl.components["U1"]["value"] == "ESP32-S3-WROOM-1-N16R8"
    assert nl.components["U1"]["fields"].get("LCSC") == "C2913202"
    assert nl.net_of_function("U1", "3V3") == "+3V3"
    assert all(nl.net_of("U1", p) == "GND" for p in (1, 40, 41))


def test_left_alone(nl):
    for gpio in (35, 36, 37, 45, 46):
        assert is_nc(esp_net(nl, gpio)), gpio


def test_boot_and_reset(nl):
    assert esp_net(nl, 0) == "BOOT" and pulls(nl, "BOOT") == [("10K", "+3V3")]
    assert not parts_between(nl, "BOOT", "GND", "C")                       # no capacitor on GPIO0
    assert between(nl, "SW1") == {"BOOT", "GND"}
    en = nl.net_of_function("U1", "EN")
    assert pulls(nl, en) == [("10K", "+3V3")]
    assert [nl.components[c]["value"] for c in parts_between(nl, en, "GND", "C")] == ["1uF"]
    assert between(nl, "SW2") == {en, "GND"}


def test_usb(nl):
    assert esp_net(nl, 19) == "USB_DN" and esp_net(nl, 20) == "USB_DP"
    for esp_side, conn_side in (("USB_DP", "USB_DP_C"), ("USB_DN", "USB_DN_C")):
        refs = parts_between(nl, esp_side, conn_side)
        assert len(refs) == 1 and nl.components[refs[0]]["value"] == "22"
    assert nl.net_of("J3", "A6") == nl.net_of("J3", "B6") == "USB_DP_C"
    assert nl.net_of("J3", "A7") == nl.net_of("J3", "B7") == "USB_DN_C"
    for cc in ("A5", "B5"):
        net = nl.net_of("J3", cc)
        assert pulls(nl, net) == [("5K1", "GND")]
    assert nl.net_of("J3", "A5") != nl.net_of("J3", "B5")                  # two separate 5.1k
    assert {nl.net_of("U7", 1), nl.net_of("U7", 3)} == {"USB_DP_C", "USB_DN_C"}
    assert nl.net_of("U7", 5) == "+3V3" and nl.net_of("U7", 2) == "GND"     # SPWR-1: D+ must not lift VBUS
    assert pulls(nl, "VBUS") == [("10K", "GND")]                               # bleeds D2's leakage
    from tests.fd import dnp_between
    assert len(dnp_between(nl, "USB_DP", "GND", "C")) == len(dnp_between(nl, "USB_DN", "GND", "C")) == 1


def test_led_uart_spare(nl):
    assert esp_net(nl, 2) == "LED"
    assert esp_net(nl, 43) == "ESP_TXD0" and esp_net(nl, 44) == "ESP_RXD0"
    tx = parts_between(nl, "ESP_TXD0", "UART_TX")
    assert len(tx) == 1 and nl.components[tx[0]]["value"] == "470"
    en = nl.net_of_function("U1", "EN")
    assert [nl.net_of("J4", p) for p in range(1, 7)] == ["UART_TX", "ESP_RXD0", en, "BOOT", "+3V3", "GND"]
    assert [nl.net_of("J5", p) for p in range(1, 5)] == ["GND", "+3V3", "GPIO18", "GPIO3"]
